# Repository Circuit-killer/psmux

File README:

12V DC power supply multiplexer.

It was primarly designed to get a 2 level redundancy power
supply. 2 input sources - a 12V AC/DC wall adapter and a
regulated solar panel - are multiplexed using an application
specific logic implemented on a microcontroller. In the case
of a redundant power supply, the logic switches from one
source to another in case of low voltage detection.

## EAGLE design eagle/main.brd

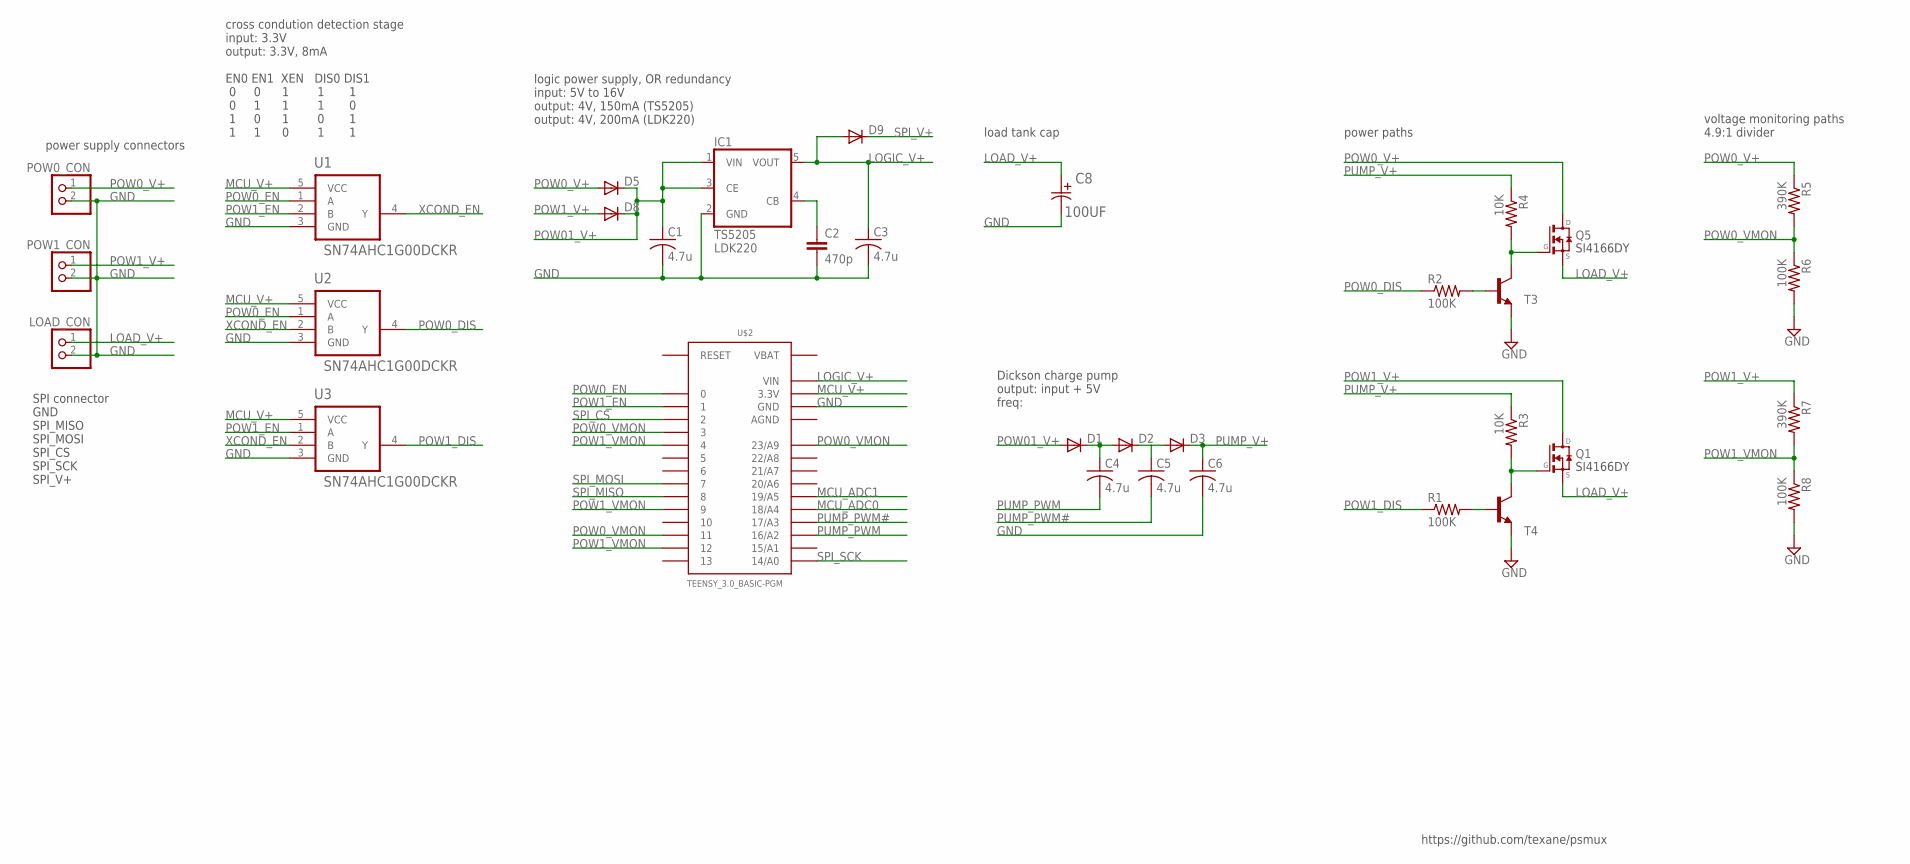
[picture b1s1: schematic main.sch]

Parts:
C1, C3, C4, C5, C6: 4.7u; C1210K
C2: 470p; C0805K
C8: 100UF; CAPAE660X800N
D1, D2, D3, D5, D8, D9: DIODE-DO214AC; DO214AC
IC1: TS5205; SOT25
LOAD_CON: PINHD-1X2; 1X02
POW0_CON, POW1_CON: PINHD-1X2; 1X02
Q1, Q5: SI4840DY; SO08-E3
R1, R2, R6, R8: 100K; M0805
R3, R4: 10K; M0805
R5, R7: 390K; M0805
T3, T4: BC817-40-NPN-SOT23-BEC; SOT23-BEC
U1, U2, U3: SN74AHC1G00DCKR; SOT65P210X110-5N
U$2: TEENSY_3.0_BASIC-PGM

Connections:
AGND: U$2.AGND
GND: C1.2, C2.2, C3.2, C6.2, C8.2, IC1.2 (GND), LOAD_CON.2, POW0_CON.2, POW1_CON.2, R6.2, R8.2, T3.E, T4.E, U1.3 (GND), U2.3 (GND), U3.3 (GND), U$2.GND, U$2.GND1 (GND)
LOAD_V+: C8.1, LOAD_CON.1, Q1.1-3 (S), Q5.1-3 (S)
LOGIC_V+: C3.1, D9.A, IC1.5 (VOUT), U$2.VIN
MCU_ADC0: U$2.18/A4
MCU_ADC1: U$2.19/A5
MCU_V+: U1.5 (VCC), U2.5 (VCC), U3.5 (VCC), U$2.3.3V, U$2.3.3V1 (3.3V)
unnamed: Q5.4 (G), R4.2, T3.C
unnamed: Q1.4 (G), R3.2, T4.C
unnamed: R1.2, T4.B
unnamed: C4.1, D1.C, D2.A
unnamed: C5.1, D2.C, D3.A
unnamed: R2.2, T3.B
unnamed: C2.1, IC1.4 (CB)
POW0_DIS: R2.1, U2.4 (Y)
POW0_EN: U1.1 (A), U2.1 (A), U$2.0
POW0_V+: D5.A, POW0_CON.1, Q5.5-8 (D), R5.1
POW0_VMON: R5.2, R6.1, U$2.3, U$2.11, U$2.23/A9
POW1_DIS: R1.1, U3.4 (Y)
POW1_EN: U1.2 (B), U3.1 (A), U$2.1
POW01_V+: C1.1, D1.A, D5.C, D8.C, IC1.1 (VIN), IC1.3 (CE)
POW1_V+: D8.A, POW1_CON.1, Q1.5-8 (D), R7.1
POW1_VMON: R7.2, R8.1, U$2.4, U$2.9, U$2.12
PUMP_PWM: C4.2, U$2.16/A2
PUMP_PWM#: C5.2, U$2.17/A3
PUMP_V+: C6.1, D3.C, R3.1, R4.1
SPI_CS: U$2.2
SPI_MISO: U$2.8
SPI_MOSI: U$2.7
SPI_SCK: U$2.14/A0
SPI_V+: D9.C
VBAT: U$2.VBAT
XCOND_EN: U1.4 (Y), U2.2 (B), U3.2 (B)

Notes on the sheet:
cross condution detection stage input: 3.3V output: 3.3V, 8mA EN0 EN1 XEN DIS0 DIS1 0 0 1 1 1 0 1 1 1 0 1 0 1 0 1 1 1 0 1 1
power supply connectors
logic power supply, OR redundancy input: 5V to 16V output: 4V, 150mA (TS5205) output: 4V, 200mA (LDK220)
load tank cap
Dickson charge pump output: input + 5V freq:
power paths
voltage monitoring paths 4.9:1 divider
SPI connector GND SPI_MISO SPI_MOSI SPI_CS SPI_SCK SPI_V+
SI4166DY
TS5205 LDK220
https://github.com/texane/psmux

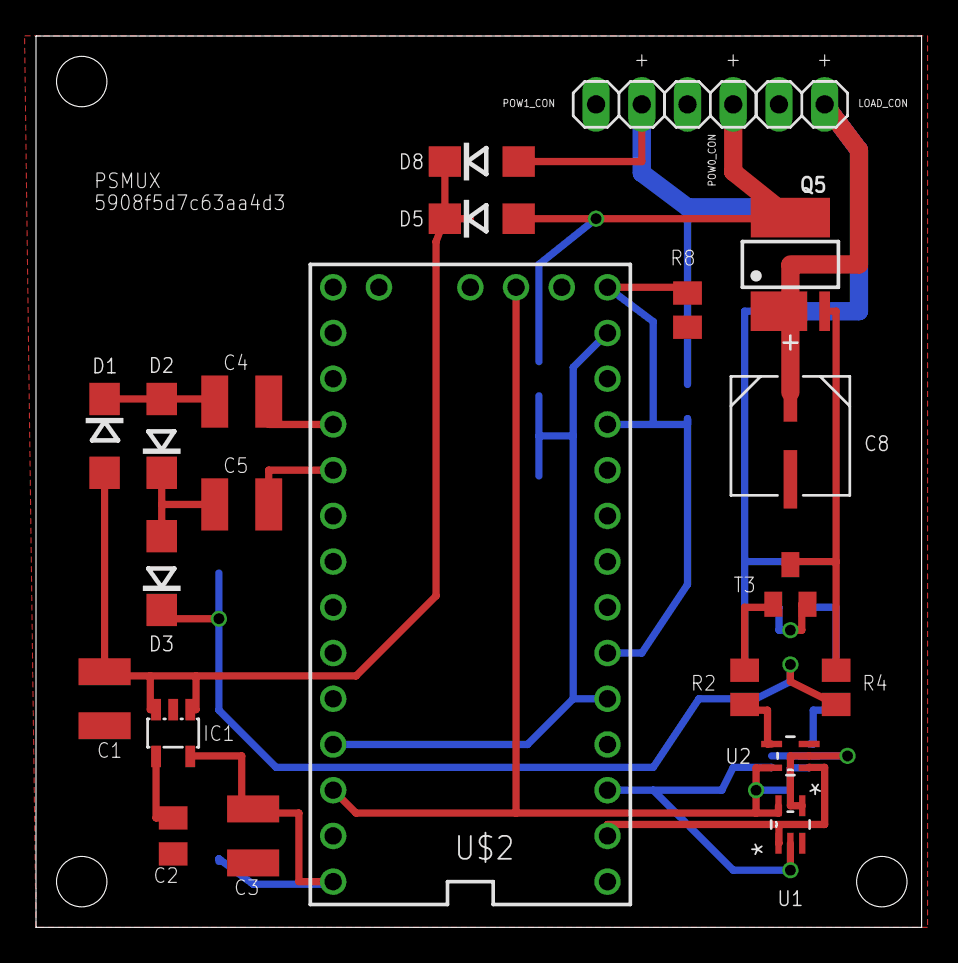
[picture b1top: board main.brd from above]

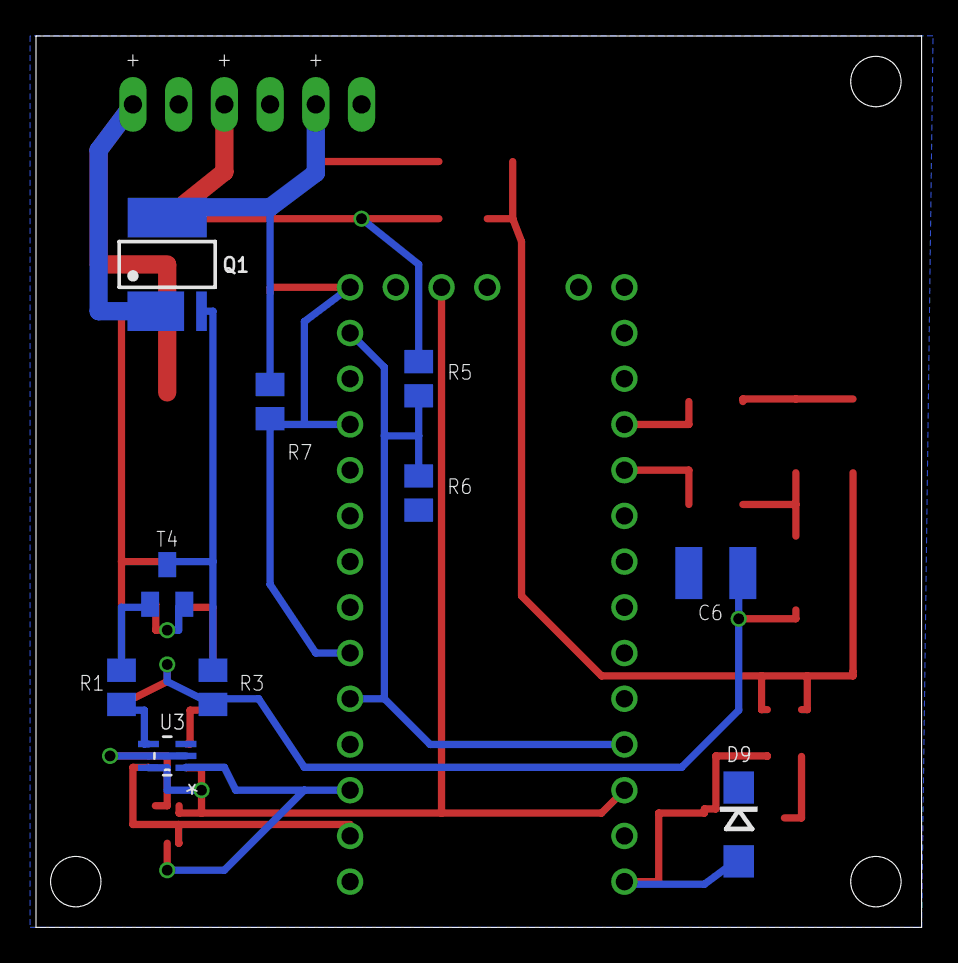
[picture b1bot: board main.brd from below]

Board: 2 copper layers, 49.2 x 49.5 mm, 33 parts (10 on the bottom side), 24 nets.

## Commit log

2015-06-08 add doc eagle spice
2015-06-08 update schematic
2015-06-08 add teensy eagle library
2015-06-08 add main.bom
2015-06-08 update schematics
2015-06-08 PWM#
2015-06-08 add TI-OPA340NA_250\@E/TI-OPA340NA_250.lbr
2015-06-08 add TI-OPA2340UA\@E/TI-OPA2340UA.lbr
2015-06-09 add src
2015-06-09 use 35,36 for FTM1_CH{0,1}
2015-06-10 disable clocking or counter not loaded
2015-06-10 pwm_freq_to_counter
2015-06-12 add board
2015-06-12 add Panasonic-EEEFK_EEEFP.lbr
2015-06-12 schottky diodes
2015-06-12 update board
2015-06-13 routing
2015-06-13 set PWM_FREQ to 50KHz
2015-06-13 add 2.2UF and ceramic caps
2015-06-13 update routing
2015-06-20 power terminals
2015-06-20 add README
2015-06-20 silkscreen
2015-06-20 frame
2015-06-20 add seeedstudio files
2015-06-20 remove schematics TODO
